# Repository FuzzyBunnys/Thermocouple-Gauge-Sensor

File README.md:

# Thermocouple Gauge Sensor
This is a project detailing a project to build a measurement computer for a thermocouple vacuum gauge that is attached to a vacuum chamber. See the [GitHub pages for more information](https://fuzzybunnys.github.io/Thermocouple-Gauge-Sensor/). 
- The BOM is the bill of materials
- The documentation file is a word document containing technical information and context
- VacuumSensorV2 is the Mecrisp-Stellaris code
- Calibration Curve is an excel file that models the curve used to generate pressure measurements
- The Thermocouple Gauge folder contains all the Kicad files related to PCB layout and design

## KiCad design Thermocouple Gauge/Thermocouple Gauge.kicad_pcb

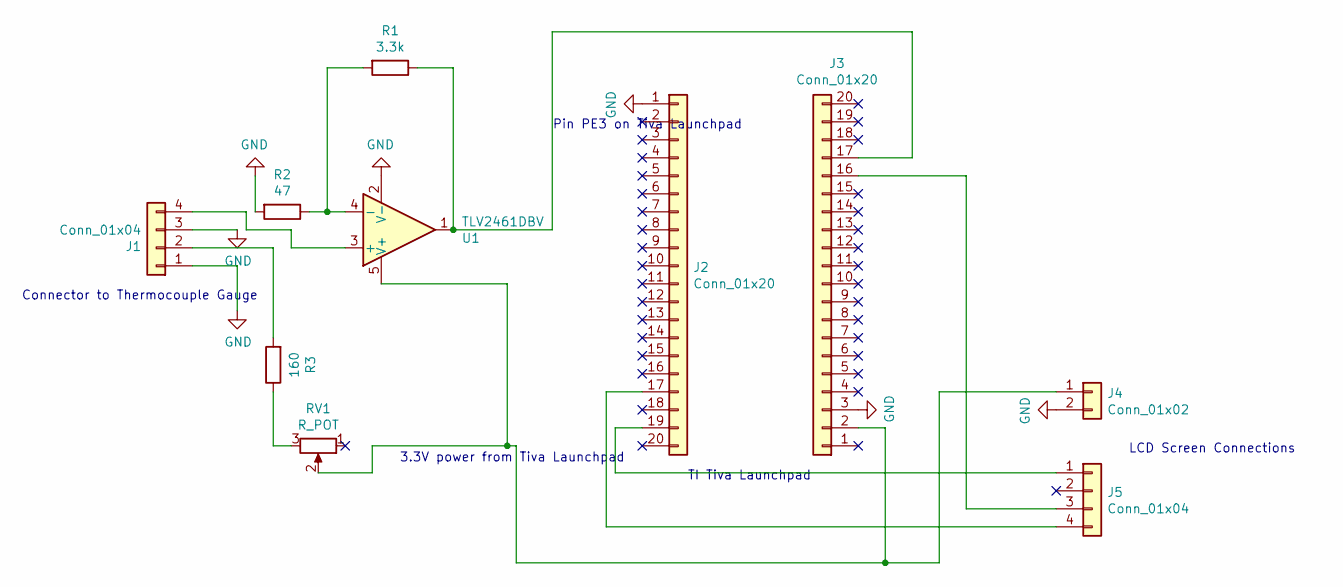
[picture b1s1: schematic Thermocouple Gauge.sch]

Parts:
J1: Conn_01x04; TerminalBlock_bornier-4_P5.08mm
J2, J3: Conn_01x20; SDL-120-X-XX_2x10
J4: Conn_01x02; PinHeader_1x02_P2.54mm_Vertical
J5: Conn_01x04; PinHeader_1x04_P2.54mm_Vertical
R1: 3.3k; R_0603
R2: 47; R_0603
R3: 160; R_0603
RV1: R_POT; Potentiometer_Trimmer_Bourns_3296W
U1: TLV2461DBV; SOT-23-5

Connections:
GND: J1.1, J1.3, J2.1, J3.3, J4.2, R2.2, U1.2 (V-)
unnamed: J1.2, R3.2
unnamed: J1.4, U1.3 (+)
unnamed: J2.17, J5.4
unnamed: J2.19, J5.1
unnamed: J3.2, J4.1, RV1.2, U1.5 (V+)
unnamed: J3.16, J5.3
unnamed: J3.17, R1.1, U1.1
unnamed: R1.2, R2.1, U1.4 (-)
unnamed: R3.1, RV1.3

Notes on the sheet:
TI Tiva Launchpad
Connector to Thermocouple Gauge
Pin PE3 on Tiva Launchpad
3.3V power from Tiva Launchpad
LCD Screen Connections

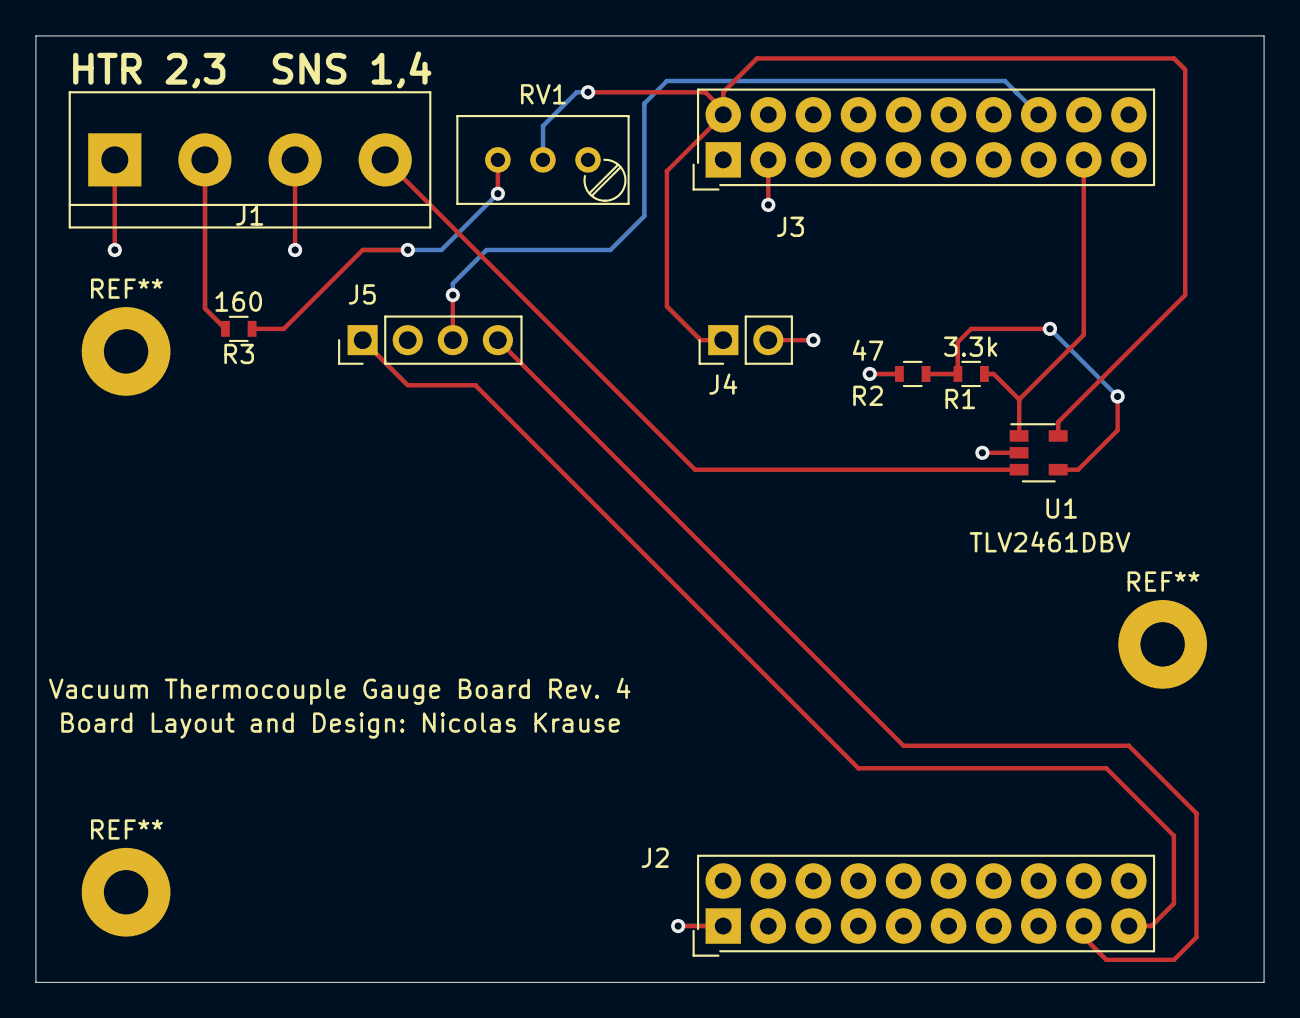
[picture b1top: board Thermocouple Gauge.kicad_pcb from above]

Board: 2 copper layers, 69.2 x 53.3 mm, 10 parts (0 on the bottom side), 10 nets.

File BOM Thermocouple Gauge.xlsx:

Vacuum Thermocouple Gauge
Part | Quantity | Cost | Total | Digikey Part Number | Newark Part Number | Link
PCB | 3 |  | 0 | n/a |  | https://oshpark.com/
Octal Connector | 2 | 10 | 20 | Ebay |  | https://www.ebay.com/itm/2pc-bakelite-octal-8pin-tube-base-f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
LCD Screen | 1 |  | 0 | n/a |  | https://www.sparkfun.com/products/16397
Single pin header strip | 1 |  |  |  | Any generic strip for pin connection will work, need 6 pins total (4 and 2)
TLV2461 - op amp | 5 | 2.8 | 14 | 296-7479-1-ND |  | https://www.digikey.ca/en/products/detail/texas-instruments/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
R1 - 3.3K | 1 |  | 0 |  | 603 SM size | Generic
R2 - 47 | 1 |  | 0 |  | 603 SM size | Generic
R3 - 160 | 1 |  | 0 |  | 603 SM size | Generic
RV1 - 1K | 1 |  | 0 |  | 10 Turn Pot | Generic
20 pin TI Connectors (2x10) | 2 |  | 0 |  | SSW-110-23-S-D | 0.100" spacing for rows and pins | Samtec 2x10 header
J1- Screw Terminal | 1 |  | 0 |  |  | Generic
TI Tiva C Launchapad | 1 |  | 0 |  |  | https://www.ti.com/tool/EK-TM4C123GXL

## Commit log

2021-03-22 Set theme jekyll-theme-minimal
2021-03-22 Add files via upload
    First commit of PCB files
2021-09-14 Add files via upload
    PCB layout, schematic and gerbers.
2021-09-14 Add files via upload
    Mecrisp-Stellaris program
